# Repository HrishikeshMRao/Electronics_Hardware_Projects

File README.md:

# Electronics_Hardware_Projects
Find my simulation files and PCB_Designs here.
This is my work in the 2nd year of Engineering where i designed numerrous PCBs and ran simulations to enhance my knowledge in electronics.

https://github.com/HrishikeshMRao/Electronics_Hardware_Projects/assets/96303885/e3d52ac2-ac10-48a9-96e2-0f7ea41b263e

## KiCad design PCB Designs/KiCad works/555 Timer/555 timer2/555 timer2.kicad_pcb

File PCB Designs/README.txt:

# Please find all the editable project files of the respective designs within.
# I have also attached jpeg files and mp4 for a clearer and easy way of viewing my works.
# Thank you for visiting. Please clone the respective folder of your interest to work on it.

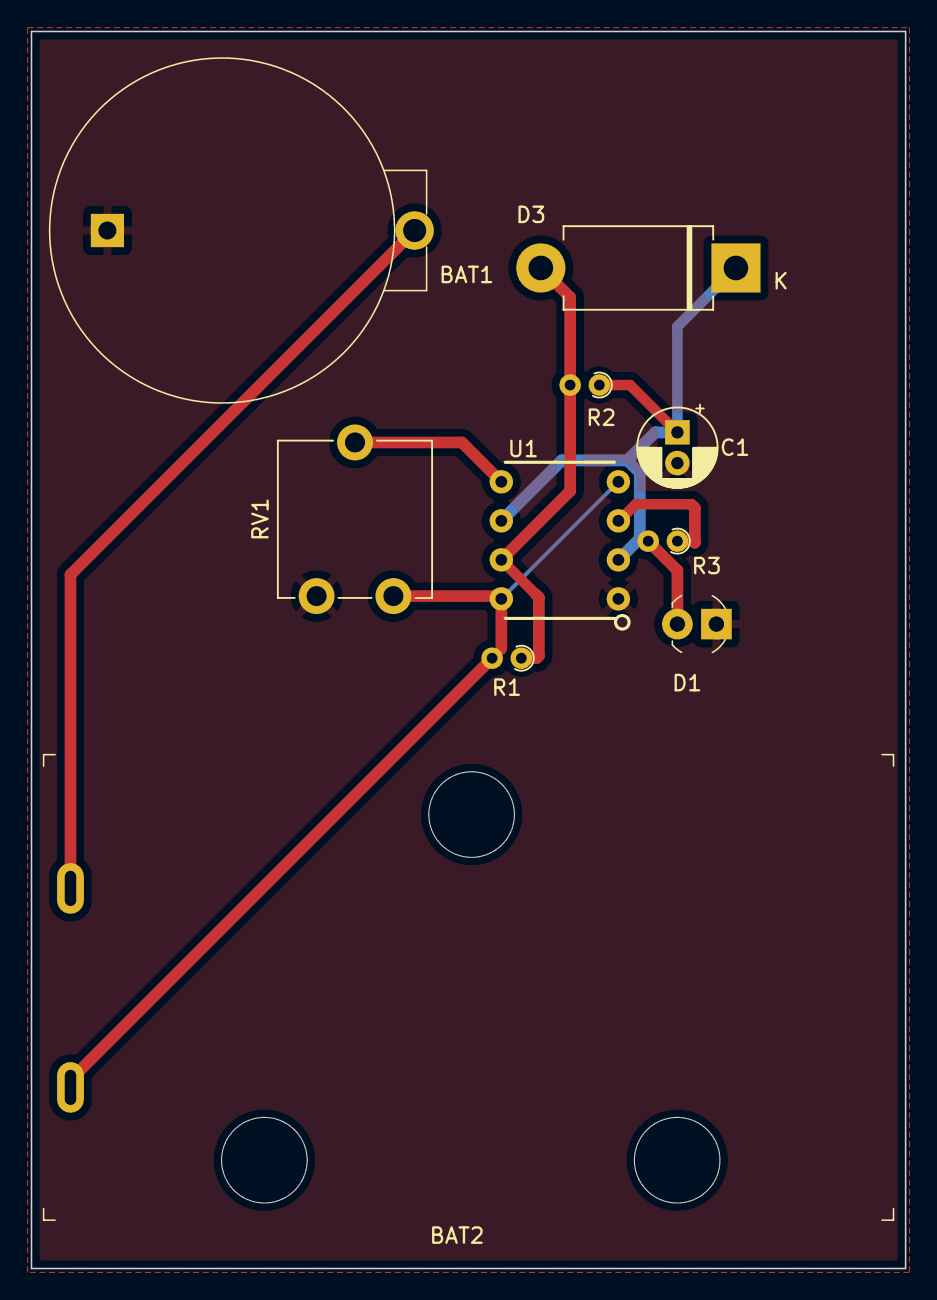
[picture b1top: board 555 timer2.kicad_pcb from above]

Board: 2 copper layers, 56.9 x 80.5 mm, 10 parts (0 on the bottom side), 6 nets.

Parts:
BAT1: 3; Battery_Holder_Coin_2032_BS-7
BAT2: 9; Battery_Holder_9V_BC9VPC-ND
C1: 10nf; CP_Radial_D5.0mm_P2.00mm
D1: RED; LED_3mm_Radial
D3: 1N5400; D_DO-201AD_P12.70mm_Horizontal
R1, R2: 470; R_Axial_DIN0204_L3.6mm_D1.6mm_P1.90mm_Vertical
R3: 220; R_Axial_DIN0204_L3.6mm_D1.6mm_P1.90mm_Vertical
RV1: 470; Potentiometer_ACP_CA9-V10_Vertical
U1: 7555; ICM7555-PDIP

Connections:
unnamed: C1.1, D1.2 (A), D3.1 (K), R2.1, R3.2, U1.2 (~TRIG), U1.6 (THRESH)
unnamed: BAT1.Neg, C1.2, D1.1 (K), RV1.3, U1.1 (GND)
unnamed: D3.2 (A), R1.1, R2.2, U1.7 (DIS)
unnamed: BAT2.POS, R1.2, RV1.1, U1.4 (~RST), U1.8 (VDD)
unnamed: R3.1, U1.3 (OUT)
unnamed: RV1.2, U1.5 (CV)

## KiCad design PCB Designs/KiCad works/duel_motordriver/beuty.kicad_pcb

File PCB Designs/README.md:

### Please find all the editable project files of the respective designs within. I have also attached jpeg files and mp4 for a clearer and easy way of viewing my works. Thank you for visiting. Please clone the respective folder of your interest to work on it.

https://github.com/HrishikeshMRao/Electronics_Hardware_Projects/assets/96303885/3500487f-d753-4d7e-9528-11d0c13f209f

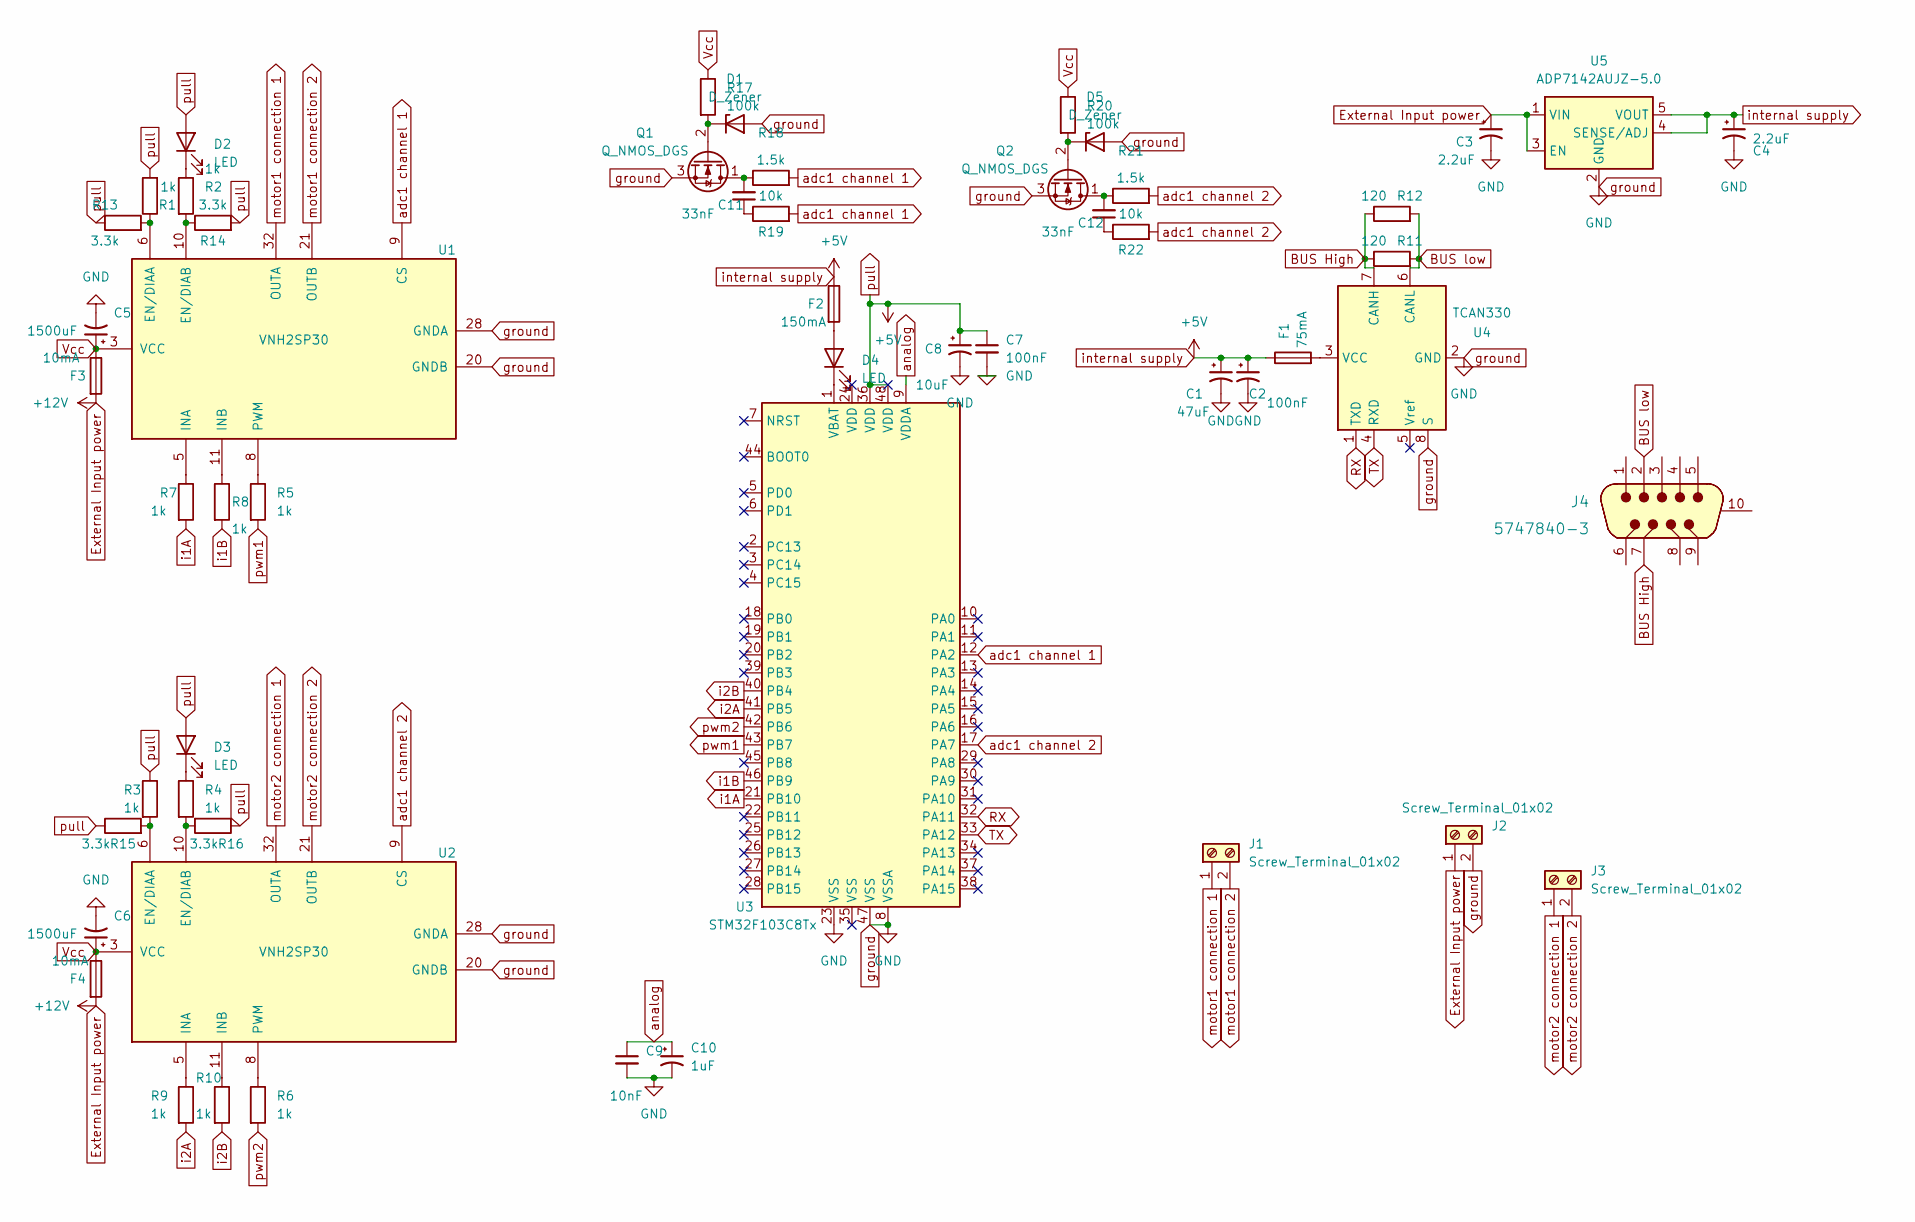
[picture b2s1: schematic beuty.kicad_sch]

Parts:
C1: 47uF; CP_Radial_D4.0mm_P1.50mm
C2: 100nF; CP_Radial_D4.0mm_P1.50mm
C3, C4: 2.2uF; CP_Radial_D4.0mm_P1.50mm
C5, C6: 1500uF; CP_Radial_D4.0mm_P1.50mm
C7: 100nF; C_Radial_D4.0mm_H5.0mm_P1.50mm
C8: 10uF; CP_Radial_D4.0mm_P1.50mm
C9: 10nF; C_Radial_D4.0mm_H5.0mm_P1.50mm
C10: 1uF; CP_Radial_D4.0mm_P1.50mm
C11, C12: 33nF; C_Radial_D4.0mm_H5.0mm_P1.50mm
D1, D5: D_Zener; D_5KP_P10.16mm_Horizontal
D2, D3, D4: LED; LED_D5.0mm_Horizontal_O1.27mm_Z3.0mm_Clear
F1: 75mA; Fuseholder_Blade_ATO_Littelfuse_Pudenz_2_Pin
F2: 150mA; Fuseholder_Blade_ATO_Littelfuse_Pudenz_2_Pin
F3, F4: 10mA; Fuseholder_Blade_ATO_Littelfuse_Pudenz_2_Pin
J1, J2, J3: Screw_Terminal_01x02; TerminalBlock_Altech_AK300-2_P5.00mm
J4: 5747840-3; DSUB-9_Jack_5747840-3; MPN 5747840-3; Digi-Key_PN A32091-ND
Q1, Q2: Q_NMOS_DGS; NEC_Molded_7x4x9mm
R1, R2, R3, R4, R5, R6, R7, R8, R9, R10: 1k; R_Axial_DIN0204_L3.6mm_D1.6mm_P1.90mm_Vertical
R11, R12: 120; R_Axial_DIN0204_L3.6mm_D1.6mm_P1.90mm_Vertical
R13, R14, R15, R16: 3.3k; R_Axial_DIN0204_L3.6mm_D1.6mm_P1.90mm_Vertical
R17, R20: 100k; R_Axial_DIN0204_L3.6mm_D1.6mm_P1.90mm_Vertical
R18, R21: 1.5k; R_Axial_DIN0204_L3.6mm_D1.6mm_P1.90mm_Vertical
R19, R22: 10k; R_Axial_DIN0204_L3.6mm_D1.6mm_P1.90mm_Vertical
U1, U2: VNH2SP30; ST_MultiPowerSO-30
U3: STM32F103C8Tx; LQFP-48_7x7mm_P0.5mm
U4: TCAN330; SOT96-1
U5: ADP7142AUJZ-5.0; TSOT-23-5

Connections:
BUS High: J4.7, R11.1, R12.1, U4.7 (CANH)
BUS low: J4.2, R11.2, R12.2, U4.6 (CANL)
External Input power: C3.1, F3.2, F4.2, J2.1, U5.1 (VIN), U5.3 (EN)
unnamed: C11.1, R19.1
unnamed: C11.2, Q1.1 (D), R18.1
unnamed: C12.1, R22.1
unnamed: C12.2, Q2.1 (D), R21.1
unnamed: D1.1 (K), Q1.2 (G), R17.2
unnamed: D2.1 (K), R2.1
unnamed: D3.1 (K), R4.1
unnamed: D4.1 (K), U3.1 (VBAT)
unnamed: D4.2 (A), F2.2
unnamed: D5.1 (K), Q2.2 (G), R20.2
unnamed: F1.2, U4.3 (VCC)
unnamed: R1.1, R13.2, U1.6 (EN/DIAA)
unnamed: R5.1, U1.8 (PWM)
unnamed: R6.1, U2.8 (PWM)
unnamed: R7.1, U1.5 (INA)
unnamed: R8.1, U1.11 (INB)
unnamed: R9.1, U2.5 (INA)
unnamed: R10.1, U2.11 (INB)
unnamed: R2.2, R14.1, U1.10 (EN/DIAB)
unnamed: R3.2, R15.2, U2.6 (EN/DIAA)
unnamed: R4.2, R16.2, U2.10 (EN/DIAB)
RX: U3.32 (PA11), U4.1 (TXD)
TX: U3.33 (PA12), U4.4 (RXD)
Vcc: C5.1, C6.1, F3.1, F4.1, R17.1, R20.1, U1.3 (VCC), U1.13 (VCC), U1.23 (VCC), U1.31 (VCC), U2.3 (VCC), U2.13 (VCC), U2.23 (VCC), U2.31 (VCC)
adc1 channel 1: R18.2, R19.2, U1.9 (CS), U3.12 (PA2)
adc1 channel 2: R21.2, R22.2, U2.9 (CS), U3.17 (PA7)
analog: C9.1, C10.1, U3.9 (VDDA)
ground: C1.2, C2.2, C3.2, C4.2, C5.2, C6.2, C7.2, C8.2, C9.2, C10.2, D1.2 (A), D5.2 (A), J2.2, Q1.3 (S), Q2.3 (S), U1.18 (GNDB), U1.19 (GNDB), U1.20 (GNDB), U1.26 (GNDA), U1.27 (GNDA), U1.28 (GNDA), U2.18 (GNDB), U2.19 (GNDB), U2.20 (GNDB), U2.26 (GNDA), U2.27 (GNDA), U2.28 (GNDA), U3.8 (VSSA), U3.23 (VSS), U3.47 (VSS), U4.2 (GND), U4.8 (S), U5.2 (GND)
i1A: R7.2, U3.21 (PB10)
i1B: R8.2, U3.46 (PB9)
i2A: R9.2, U3.41 (PB5)
i2B: R10.2, U3.40 (PB4)
internal supply: C1.1, C2.1, C4.1, C7.1, C8.1, D2.2 (A), D3.2 (A), F1.1, F2.1, R1.2, R3.1, R13.1, R14.2, R15.1, R16.1, U3.36 (VDD), U3.48 (VDD), U5.4 (SENSE/ADJ), U5.5 (VOUT)
motor1 connection 1: J1.1, U1.1 (OUTA), U1.25 (OUTA), U1.30 (OUTA), U1.32 (OUTA)
motor1 connection 2: J1.2, U1.15 (OUTB), U1.16 (OUTB), U1.21 (OUTB), U1.33 (OUTB)
motor2 connection 1: J3.1, U2.1 (OUTA), U2.25 (OUTA), U2.30 (OUTA), U2.32 (OUTA)
motor2 connection 2: J3.2, U2.15 (OUTB), U2.16 (OUTB), U2.21 (OUTB), U2.33 (OUTB)
pwm1: R5.2, U3.43 (PB7)
pwm2: R6.2, U3.42 (PB6)

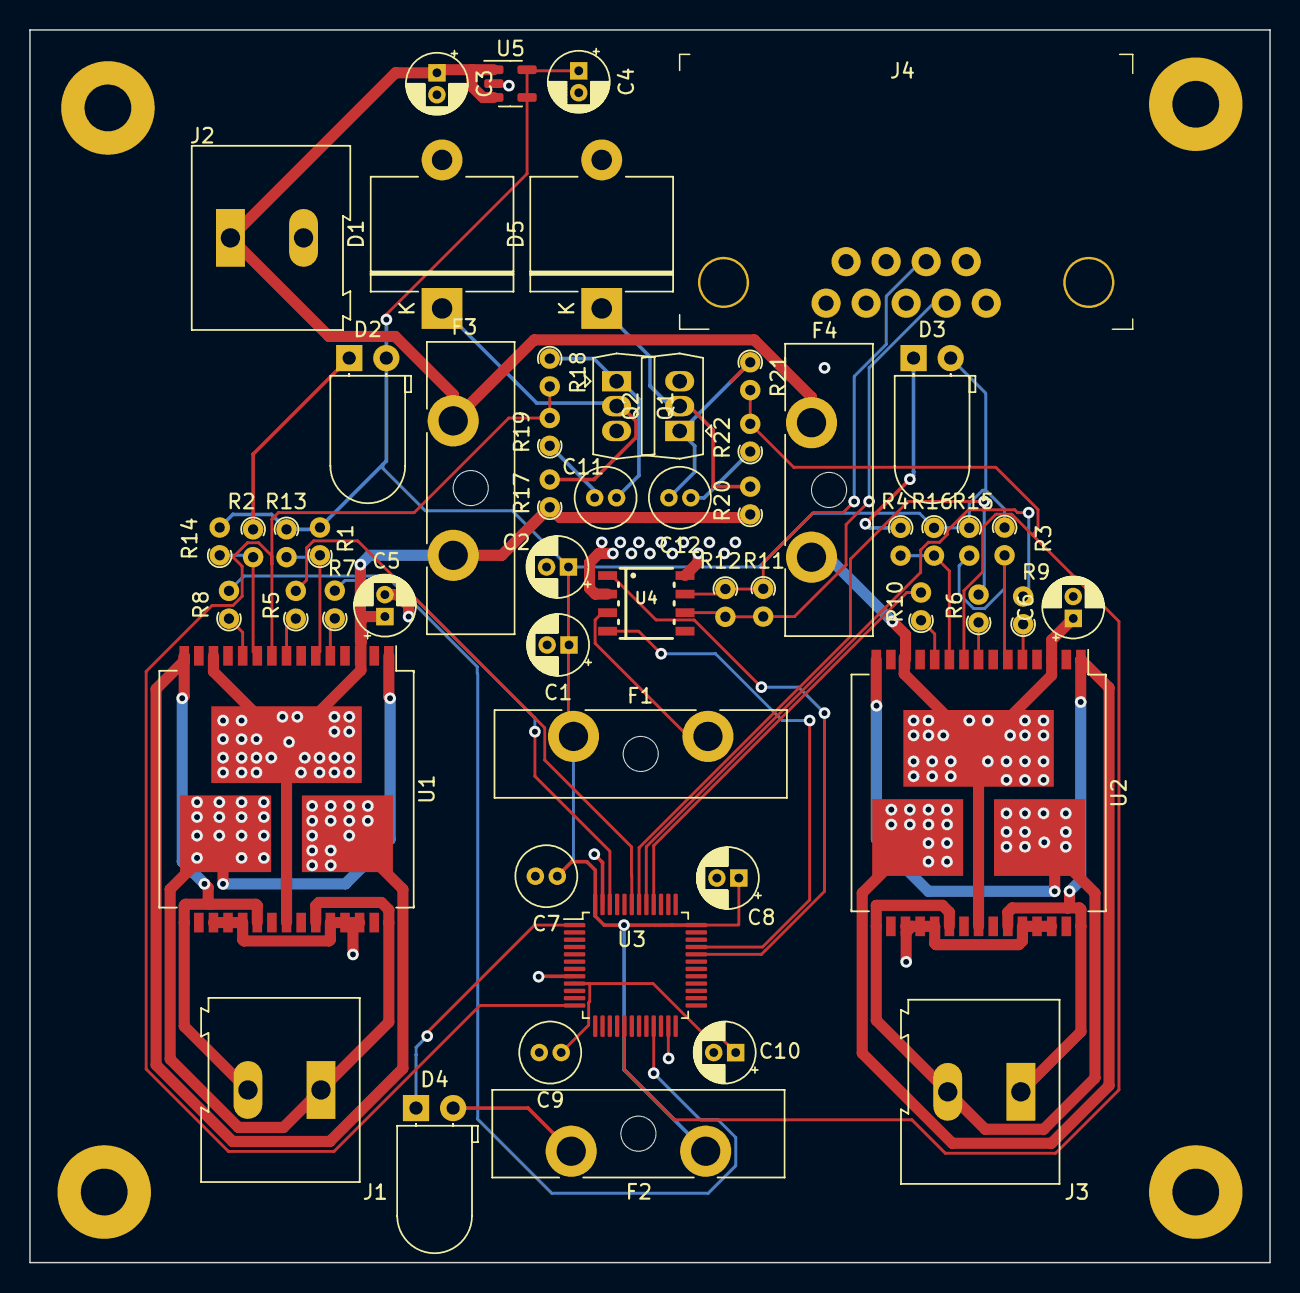
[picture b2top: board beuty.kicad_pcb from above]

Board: 4 copper layers, 84.8 x 84.3 mm, 54 parts (0 on the bottom side), 42 nets.

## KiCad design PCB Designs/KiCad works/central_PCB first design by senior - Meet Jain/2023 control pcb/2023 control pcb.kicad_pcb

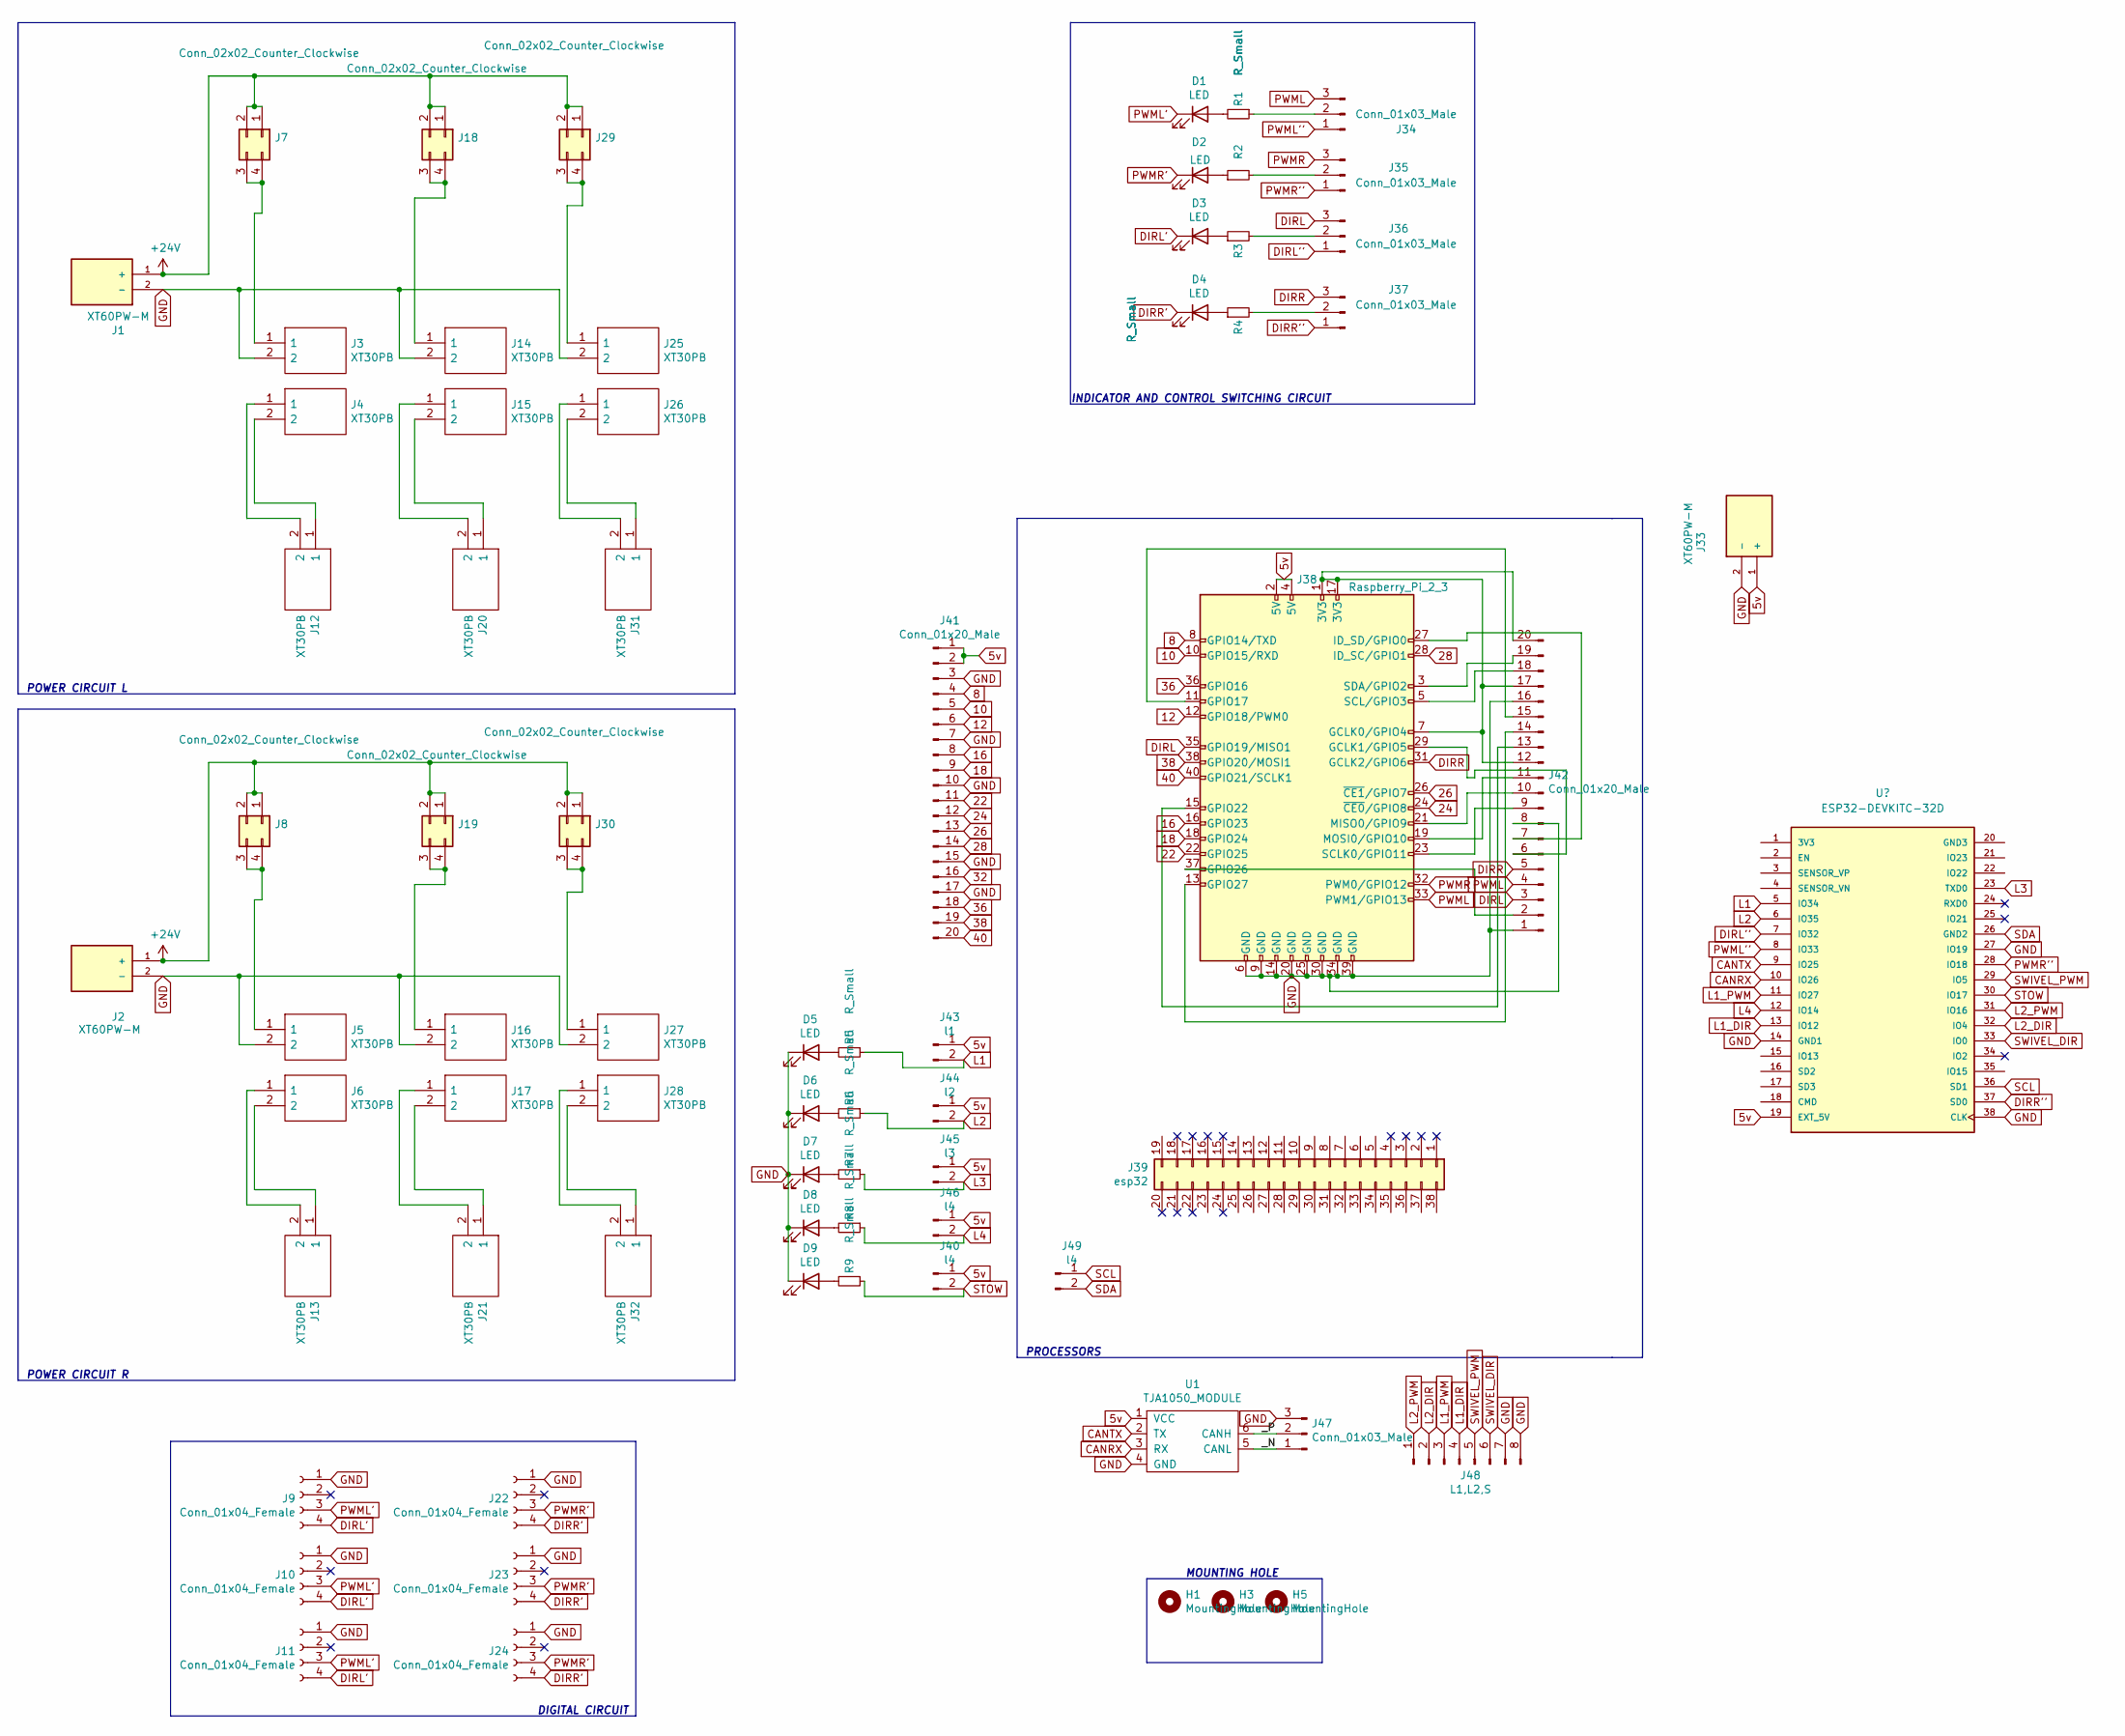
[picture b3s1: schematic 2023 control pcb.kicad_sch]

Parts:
D1, D2, D3, D4, D5, D6, D7, D8, D9: LED; LED_0805_2012Metric_Pad1.15x1.40mm_HandSolder
H1, H3, H5: MountingHole; MountingHole_5.3mm_M5_DIN965
J1, J2, J33: XT60PW-M; AMASS_XT60PW-M; PARTREV V1.2
J3, J4, J5, J6, J12, J13, J14, J15, J16, J17, J20, J21, J25, J26, J27, J28, J31, J32: XT30PB; Manufacturer_Part_Number XT30PB
J7, J8, J18, J19, J29, J30: Conn_02x02_Counter_Clockwise; fuseholder_355720
J9, J10, J11, J22, J23, J24: Conn_01x04_Female; JST_PH_B4B-PH-K_1x04_P2.00mm_Vertical
J34, J35, J36, J37: Conn_01x03_Male; PinSocket_1x03_P2.54mm_Vertical
J38: Raspberry_Pi_2_3; MODULE_RASPBERRY_PI_3_MODEL_B+
J39: esp32
J40, J46, J49: l4; Altech_AK300_1x02_P5.00mm_45-Degree
J41, J42: Conn_01x20_Male; PinHeader_1x20_P2.54mm_Vertical
J43: l1; Altech_AK300_1x02_P5.00mm_45-Degree
J44: l2; Altech_AK300_1x02_P5.00mm_45-Degree
J45: l3; Altech_AK300_1x02_P5.00mm_45-Degree
J47: Conn_01x03_Male; TerminalBlock_Altech_AK300-3_P5.00mm
J48: L1,L2,S; JST_EH_S8B-EH_1x08_P2.50mm_Horizontal
R1, R2, R3, R4, R5, R6, R7, R8, R9: R_Small; R_0805_2012Metric_Pad1.20x1.40mm_HandSolder
U1: TJA1050_MODULE

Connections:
5v: J33.1 (+), J38.2 (5V), J38.4 (5V), J39.19, J40.1, J41.1, J41.2, J43.1, J44.1, J45.1, J46.1, U1.1 (VCC)
8: J38.8 (GPIO14/TXD), J41.4
10: J38.10 (GPIO15/RXD), J41.5
12: J38.12 (GPIO18/PWM0), J41.6
16: J38.16 (GPIO23), J41.8
18: J38.18 (GPIO24), J41.9
22: J38.22 (GPIO25), J41.11
24: J38.24 (~CE0/GPIO8), J41.12
26: J38.26 (~CE1/GPIO7), J41.13
28: J38.28 (ID_SC/GPIO1), J41.14
32: J41.16
36: J38.36 (GPIO16), J41.18
38: J38.38 (GPIO20/MOSI1), J41.19
40: J38.40 (GPIO21/SCLK1), J41.20
+24V: J1.1 (+), J2.1 (+), J7.1, J7.2, J8.1, J8.2, J18.1, J18.2, J19.1, J19.2, J29.1, J29.2, J30.1, J30.2
/_N: J47.1, U1.5 (CANL)
/_P: J47.2, U1.6 (CANH)
CANRX: J39.10, U1.3 (RX)
CANTX: J39.9, U1.2 (TX)
DIRL: J36.3, J38.35 (GPIO19/MISO1), J42.3
DIRL': D3.1 (K), J9.4, J10.4, J11.4
DIRL'': J36.1, J39.7
DIRR: J37.3, J38.31 (GCLK2/GPIO6), J42.5
DIRR': D4.1 (K), J22.4, J23.4, J24.4
DIRR'': J37.1, J39.37
GND: D5.1 (K), D6.1 (K), D7.1 (K), D8.1 (K), D9.1 (K), J1.2 (-), J2.2 (-), J3.2, J5.2, J9.1, J10.1, J11.1, J14.2, J16.2, J22.1, J23.1, J24.1, J25.2, J27.2, J33.2 (-), J38.6 (GND), J38.9 (GND), J38.14 (GND), J38.20 (GND), J38.25 (GND), J38.30 (GND), J38.34 (GND), J38.39 (GND), J39.14, J39.32, J39.38, J41.3, J41.7, J41.10, J41.15, J41.17, J42.1, J42.8, J42.16, J47.3, J48.7, J48.8, U1.4 (GND)
L1: J39.5, J43.2, R5.1
L1_DIR: J39.13, J48.4
L1_PWM: J39.11, J48.3
L2: J39.6, J44.2, R6.1
L2_DIR: J39.27, J48.2
L2_PWM: J39.28, J48.1
L3: J39.23, J45.2, R7.1
L4: J39.12, J46.2, R8.1
unnamed: D1.2 (A), R1.2
unnamed: D2.2 (A), R2.1
unnamed: D3.2 (A), R3.1
unnamed: D4.2 (A), R4.1
unnamed: D5.2 (A), R5.2
unnamed: D6.2 (A), R6.2
unnamed: D7.2 (A), R7.2
unnamed: D8.2 (A), R8.2
unnamed: D9.2 (A), R9.2
unnamed: J3.1, J7.3, J7.4
unnamed: J5.1, J8.3, J8.4
unnamed: J4.2, J12.1
unnamed: J4.1, J12.2
unnamed: J6.2, J13.1
unnamed: J6.1, J13.2
unnamed: J14.1, J18.3, J18.4
unnamed: J15.1, J20.2
unnamed: J15.2, J20.1
unnamed: J16.1, J19.3, J19.4
unnamed: J17.1, J21.2
unnamed: J17.2, J21.1
unnamed: J25.1, J29.3, J29.4
unnamed: J26.1, J31.2
unnamed: J26.2, J31.1
unnamed: J27.1, J30.3, J30.4
unnamed: J28.1, J32.2
unnamed: J28.2, J32.1
unnamed: J34.2, R1.1
unnamed: J35.2, R2.2
unnamed: J36.2, R3.2
unnamed: J37.2, R4.2
unnamed: J38.1 (3V3), J38.7 (GCLK0/GPIO4), J38.17 (3V3), J42.12, J42.17, J42.20
unnamed: J38.3 (SDA/GPIO2), J42.19
unnamed: J38.5 (SCL/GPIO3), J42.18
unnamed: J38.11 (GPIO17), J42.15
unnamed: J38.13 (GPIO27), J42.14
unnamed: J38.15 (GPIO22), J42.13
unnamed: J38.19 (MOSI0/GPIO10), J42.11
unnamed: J38.21 (MISO0/GPIO9), J42.10
unnamed: J38.23 (SCLK0/GPIO11), J42.9
unnamed: J38.27 (ID_SD/GPIO0), J42.7
unnamed: J38.29 (GCLK1/GPIO5), J42.6
unnamed: J38.37 (GPIO26), J42.2
PWML: J34.3, J38.33 (PWM1/GPIO13), J42.4
PWML': D1.1 (K), J9.3, J10.3, J11.3
PWML'': J34.1, J39.8
PWMR: J35.3, J38.32 (PWM0/GPIO12)
PWMR': D2.1 (K), J22.3, J23.3, J24.3
PWMR'': J35.1, J39.31
SCL: J39.36, J49.1
SDA: J39.33, J49.2
STOW: J39.29, J40.2, R9.1
SWIVEL_DIR: J39.26, J48.6
SWIVEL_PWM: J39.30, J48.5

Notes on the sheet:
INDICATOR AND CONTROL SWITCHING CIRCUIT
DIGITAL CIRCUIT
MOUNTING HOLE
POWER CIRCUIT L
POWER CIRCUIT R
PROCESSORS

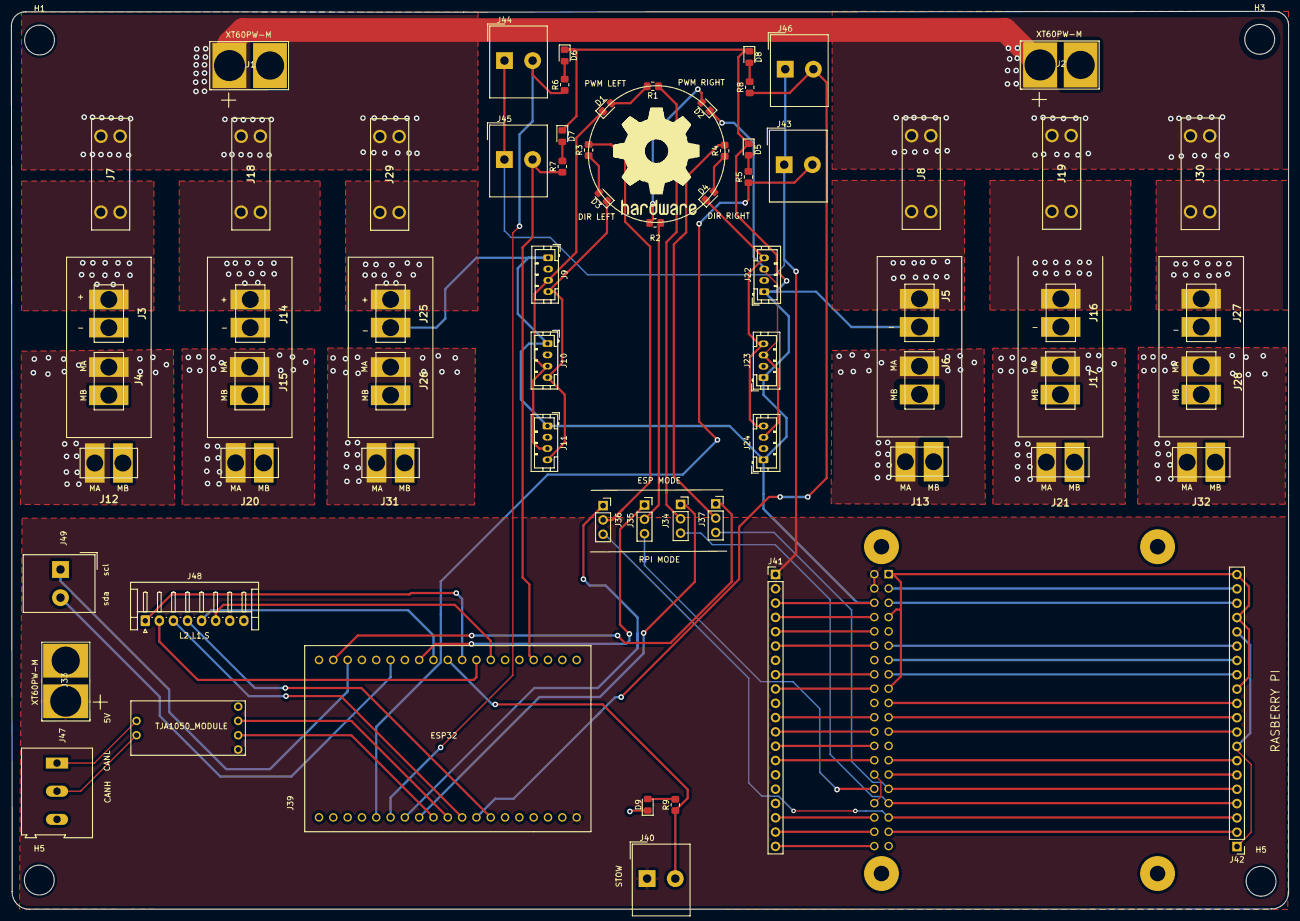
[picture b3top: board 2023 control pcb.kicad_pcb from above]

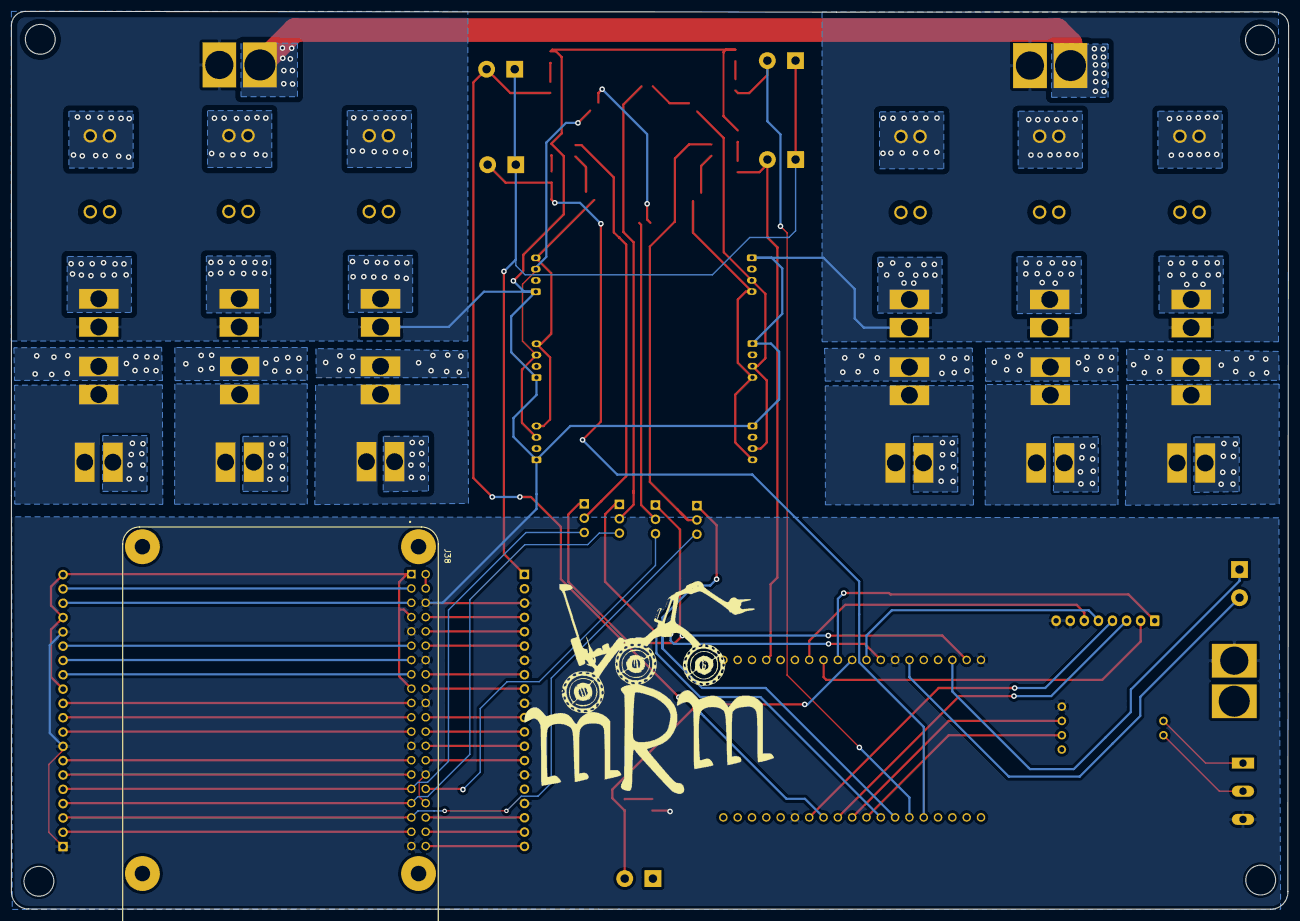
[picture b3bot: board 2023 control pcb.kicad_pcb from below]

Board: 2 copper layers, 226.6 x 159.3 mm, 73 parts (2 on the bottom side), 87 nets.

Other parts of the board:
G5: LOGO; MRM_LOGO
H5#2: MountingHole; MountingHole_5.3mm_M5_DIN965

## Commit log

2023-07-26 Add files via upload
    initial commit schematic and 3d
2023-07-26 Add files via upload
    node mcu both designs
2023-07-26 Add files via upload
    lora module on arduino shield with UFL antenna and voltage regulator
2023-07-26 added project files
    added project files
2023-07-26 Create README.txt
    added a readme
2023-09-13 Update README.md
    added vedio
2023-09-26 Update README.md
    added a vedio
